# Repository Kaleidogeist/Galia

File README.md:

# Galia
Modular split ergonomic keyboard system with each half consisting of a central motherboard and a hot-swappable key cluster daughterboard to allow for maximum flexibility.

### Motherboard

- Current version: V0.4.
- Schematic [here](https://kicanvas.org/?repo=https%3A%2F%2Fgithub.com%2Fghostlybutterfly%2FGalia%2Fblob%2FV0_dev%2FMotherboard%2FMotherboard.kicad_sch). 
- Board layout [here](https://kicanvas.org/?repo=https%3A%2F%2Fgithub.com%2Fghostlybutterfly%2FGalia%2Ftree%2FV0_dev%2FMotherboard).
### Daughterboard (Cantaloupe)
Current version: N/A (wip).

## Disclaimer
This keyboard is licensed under [CERN-OHL-S-2.0](https://cern-ohl.web.cern.ch/) and is compatible with both [QMK Firmware](https://qmk.fm/) and [ZMK Firmware](https://zmk.dev).

## Key Features
### Motherboard
* Fully reversible, compact (32.0x50.0mm), and designed to fit onto the top inner corner of a split keyboard.
* On-board STM32G0B1CCU7 processor.
* ESD-protected USB-C input port and USB-C split comms port.
* Connects to daughterboard through fully ESD-protected 2.54mm pitch 02x06 pogo header.
* SPI and USART lines terminated with 22ohm to reduce ringing, overshoot and EMI, and improve signal integrity.
* VBUS input rail limited to ~469mA and 5V output rail limited to ~179mA through the use of TPS2553-1 current limiting switches with reverse voltage protection. VBUS requires power cycling to restart the device upon overcurrent, +5V can be power-cycled through firmware with EN pin controlled through firmware to reduce RGB LED quiescent current draw.
* 4-layer (signal/ground/power/signal) PCB and star ground connection point in between USB port shields.
* [Paw-Connect](https://github.com/LeoDJ/Paw-Connect) TC-2030NL SWD header for debugging purposes.
* On-board single-button reset circuit.
* JLC basic assembly compatible as long as USB ports are not soldered on.

### Daughterboard (TBC)
* Matrix scan planned to be implemented through 74HC595 SIPO shift registers for low power draw and compatibility with ZMK interrupt functionality.
* Also compatible with charlieplex, duplex, and standard matrix layouts.
* WS2812 and AP102 (QMK only) LED support.
* Additional [VIK](https://github.com/sadekbaroudi/vik) header support if desired.

## Pogo header pinout
| Function/description                 | Pin name | Row 1 | Row 2 | Pin name | Function/description                  |
| ------------------------------------ | -------- | ----- | ----- | -------- | ------------------------------------- |
| USART2_TX/ADC1_IN2/TIM2_CH3          | A2       | GPIO1 | CS    | B9       | SPI2_NSS/I2C1_SDA/USART3_RX/TIM4_CH4  |
| USART2_RX/ADC1_IN3/TIM2_CH4          | A3       | GPIO2 | SCK   | B8       | SPI2_SCK/I2C1_SCL/USART3_TX/TIM4_CH3  |
| SPI1_SCK/ADC1_IN5/TIM2_CH1           | A5       | GPIO3 | MOSI  | B7       | SPI2_MOSI/I2C1_SDA/USART1_RX/TIM4_CH2 |
| SPI1_MISO/ADC1_IN6/I2C2_SDA/TIM3_CH1 | A6       | GPIO4 | MISO  | B6       | SPI2_MISO/I2C1_SCL/USART1_TX/TIM1_CH3 |
| SPI1_MOSI/ADC1_IN7/I2C2_SCL/TIM3_CH2 | A7       | GPIO5 | +5V   | N/A      | ~207mA max draw by daughterboard      |
| 200mA max draw by this side overall  | N/A      | VDD   | GND   | A7       | GND                                   |

## Changelog
* 2026/10/01: Changed library name and updated paths.
* 2026/09/30: V0.4 motherboard update complete. Removed guard ring around the edge of the board. Moved reset button and pogo header down the board. Increased length back to 50mm to allow for an E73-2G4M08S1C version to be developed if desired. Simplified reset circuit - doesn't use the Acheron version anymore. Reduced number of pins in pogo header, as the largest available ones are 2x06. Pinout of pogo header changed to greatly simplify routing - no longer VIK-compliant. Signalis reference and Paw-Connect added back. Changed file structure.
* 2026/09/26: V0.3 motherboard update complete. Reduced size again, rerouted board and changed shape slightly. Removed one mounting hole and centred the other between the USB ports. Changed input fuse and external +5V output to TPS2553-1 latching power switch with reverse voltage/current protection. Removed AO3401 and LMV321 discrete reverse current protection at VBUS input. Reduced size of VBUS and VSPLIT ferrite bead and transistors in the Acheron reset circuit. Made Acheron reset circuit reach DFU faster. 
* 2026/09/21: V0.2 motherboard update complete. Significantly decreased size. GPIO3, GPIO4 and GPIO5 pins changed. Increased size of pogo pin header pads. Removed extra IO header. Replaced 2x03 2.54mm programming header and TC2030-NL with 2x05 1.27mm Samtec IDC header. Replaced reset switch with smaller Alps SKSNLP mid-mount switch. Added layer marker. Changed repository file structure.
* 2026/09/17: Fixed gap in guard rail.
* 2026/09/16: V0.1 motherboard initial commit.

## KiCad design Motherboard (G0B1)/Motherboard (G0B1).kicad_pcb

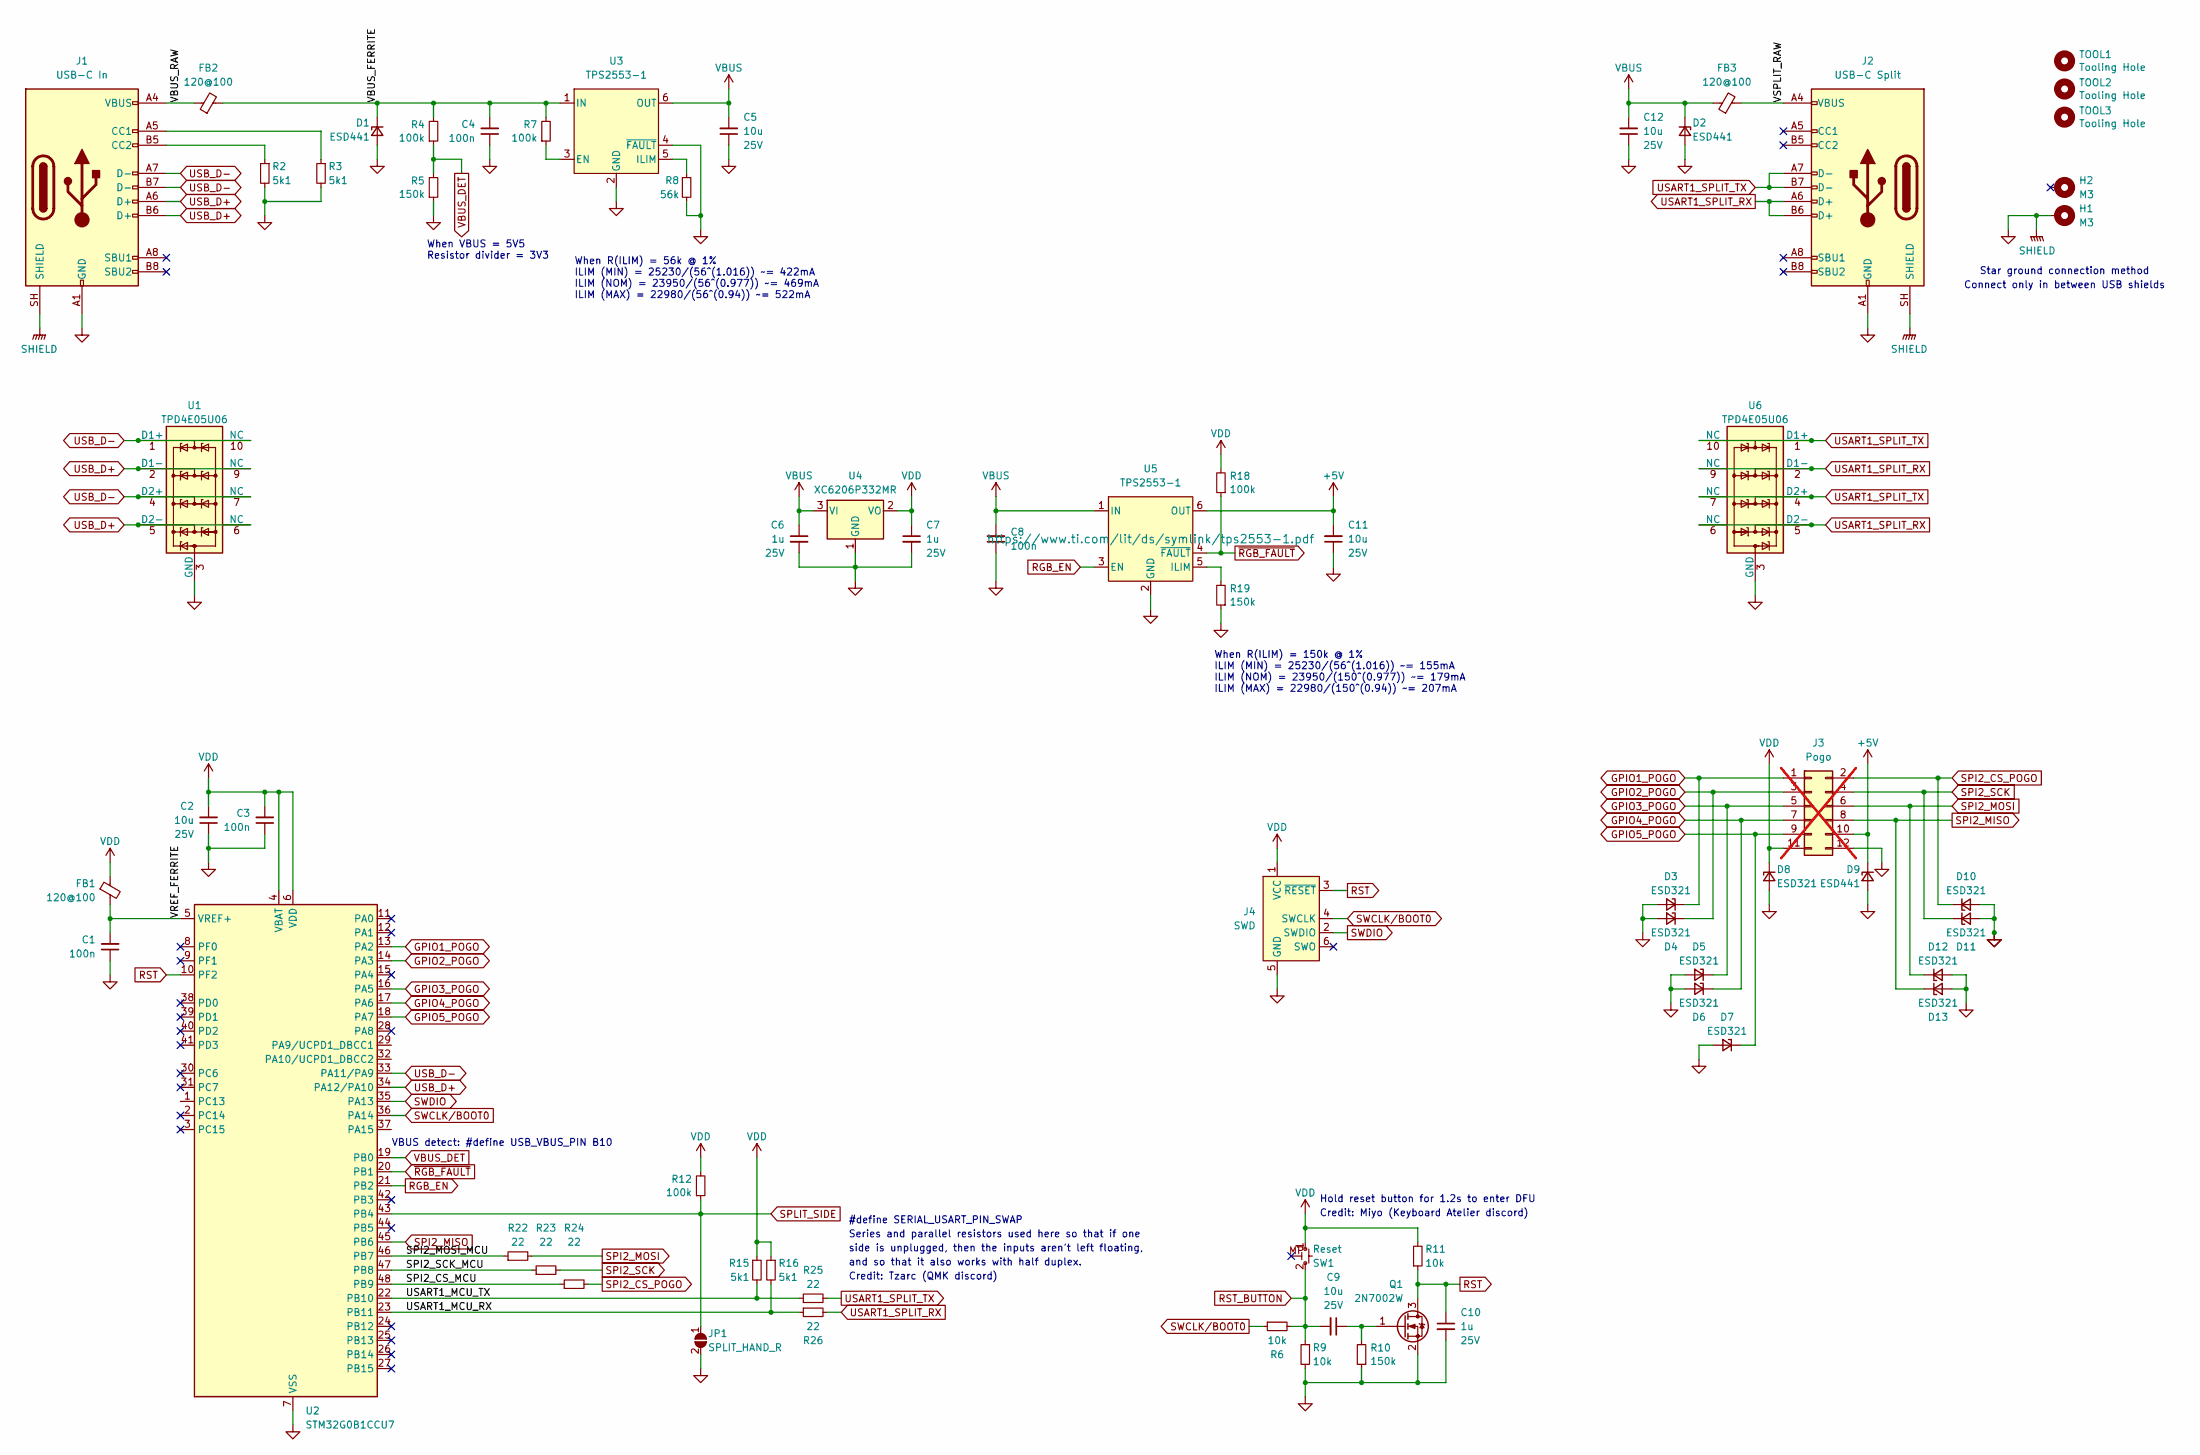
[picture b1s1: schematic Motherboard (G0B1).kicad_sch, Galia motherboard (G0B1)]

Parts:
C1, C3, C4, C8: 100n; C_0402_1005Metric; Rating 50V; MPN CL05B104KB54PNC; LCSC C307331
C2, C5, C9, C11, C12: 10u; C_0603_1608Metric; Rating 25V; MPN CL10A106MA8NRNC; LCSC C96446
C6, C7, C10: 1u; C_0402_1005Metric; Rating 25V; MPN CL05A105KA5NQNC; LCSC C52923
D1, D2, D9: ESD441; X1SON_0.6x1mm_P0.65mm_Texas_DPY0002A; Rating 7V breakdown; MPN ESD441DPYR; LCSC C53161160
D3, D4, D5, D6, D7, D8, D10, D11, D12, D13: ESD321; X1SON_0.6x1mm_P0.65mm_Texas_DPY0002A; Rating 4V5 breakdown; MPN ESD321DPYR; LCSC C2868952
FB1, FB2, FB3: 120@100; L_0402_1005Metric; MPN MPZ1005S121ET000; LCSC C275477
H1, H2: M3; MountingHole_3.2mm_M3_Pad_Via; MPN N/A; LCSC N/A
J1: USB-C In; USB_C_Receptacle_Molex_2169900001; MPN GT-USB-7014D; LCSC C2843969
J2: USB-C Split; USB_C_Receptacle_Molex_2169900001; MPN GT-USB-7014D; LCSC C2843969
J3: Pogo; PinHeader_2x06_2.54mm_MillMax_PogoTarget_419-10-212-00-0010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; not fitted
J4: SWD; Paw-Connect_RevB_TC2030-IDC-NL_2x03_P1.27mm_Vertical
JP1: SPLIT_HAND_R; SolderJumper-2_P1.2mm_Open_Pad1.0x1.4mm; MPN N/A; LCSC N/A
Q1: 2N7002W; SOT-323_SC-70-3; MPN 2N7002W; LCSC C7420322
R2, R3, R15, R16: 5k1; R_0402_1005Metric; MPN 0402WGF5101TCE; LCSC C25905
R4, R7, R12, R18: 100k; R_0402_1005Metric; MPN 0402WGF1003TCE; LCSC C25741
R5, R10, R19: 150k; R_0402_1005Metric; MPN 0402WGF1503TCE; LCSC C25755
R6, R9, R11: 10k; R_0402_1005Metric; MPN 0402WGF1002TCE; LCSC C25744
R8: 56k; R_0402_1005Metric; MPN 0402WGF5602TCE; LCSC C25796
R22, R23, R24, R25, R26: 22; R_0402_1005Metric; MPN 0402WGF220JTCE; LCSC C25092
SW1: Reset; SW_Alps_SKSNLM_SKSNLP; MPN SKSNLPE010; LCSC C53113391
TOOL1, TOOL2, TOOL3: Tooling Hole; MountingHole_JLC-Tooling; MPN N/A; LCSC N/A
U1, U6: TPD4E05U06; USON-10_2.5x1.0mm_P0.5mm; MPN TPD4E05U06QDQARQ1; LCSC C81353
U2: STM32G0B1CCU7; QFN-48-1EP_7x7mm_P0.5mm_EP5.6x5.6mm; MPN STM32G0B1CCU7; LCSC C29759424
U3, U5: TPS2553-1; WSON-6-1EP_2x2mm_P0.65mm_EP1x1.6mm; MPN TPS2553DRVR-1; LCSC C411878
U4: XC6206P332MR; SOT-23-3; MPN XC6206P332MR-G; LCSC C5446

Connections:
+5V: C11.2, D9.1 (K), J3.10, U5.6 (OUT)
/SPI2_CS_MCU: R24.1, U2.48 (PB9)
/SPI2_MOSI_MCU: R22.1, U2.46 (PB7)
/SPI2_SCK_MCU: R23.1, U2.47 (PB8)
/USART1_MCU_RX: R16.2, R26.1, U2.23 (PB11)
/USART1_MCU_TX: R15.2, R25.1, U2.22 (PB10)
/VBUS_FERRITE: C4.2, D1.1 (K), FB2.2, R4.2, R7.2, U3.1 (IN)
/VBUS_RAW: FB2.1, J1.A4 (VBUS), J1.A9 (VBUS), J1.B4 (VBUS), J1.B9 (VBUS)
/VREF_FERRITE: C1.2, FB1.2, U2.5 (VREF+)
/VSPLIT_RAW: FB3.2, J2.A4 (VBUS), J2.A9 (VBUS), J2.B4 (VBUS), J2.B9 (VBUS)
GND: C1.1, C2.1, C3.1, C4.1, C5.1, C6.2, C7.2, C8.1, C10.2, C11.1, C12.1, D1.2 (A), D2.2 (A), D3.2 (A), D4.2 (A), D5.2 (A), D6.2 (A), D7.2 (A), D8.2 (A), D9.2 (A), D10.2 (A), D11.2 (A), D12.2 (A), D13.2 (A), H1.1 (1_1), J1.A1 (GND), J1.A12 (GND), J1.B1 (GND), J1.B12 (GND), J1.SH (SHIELD), J2.A1 (GND), J2.A12 (GND), J2.B1 (GND), J2.B12 (GND), J2.SH (SHIELD), J3.12, J4.5 (GND), JP1.2 (B), Q1.2 (S), R2.2, R3.2, R5.1, R8.2, R9.2, R10.1, R19.1, U1.3 (GND), U1.8 (GND), U2.7 (VSS), U2.49 (VSS), U3.2 (GND), U3.4 (~FAULT), U3.7 (EP), U4.1 (GND), U5.2 (GND), U5.7 (EP), U6.3 (GND), U6.8 (GND)
GPIO1_POGO: D3.1 (K), J3.1, U2.13 (PA2)
GPIO2_POGO: D4.1 (K), J3.3, U2.14 (PA3)
GPIO3_POGO: D5.1 (K), J3.5, U2.16 (PA5)
GPIO4_POGO: D6.1 (K), J3.7, U2.17 (PA6)
GPIO5_POGO: D7.1 (K), J3.9, U2.18 (PA7)
unnamed: J1.A5 (CC1), R3.1
unnamed: J1.B5 (CC2), R2.1
unnamed: C9.1, Q1.1 (G), R10.2
unnamed: R7.1, U3.3 (EN)
unnamed: R8.1, U3.5 (ILIM)
unnamed: R19.2, U5.5 (ILIM)
RGB_EN: U2.21 (PB2), U5.3 (EN)
RST: C10.1, J4.3 (~RESET), Q1.3 (D), R11.1, U2.10 (PF2)
RST_BUTTON: C9.2, R6.2, R9.1, SW1.2 (B)
SPI2_CS_POGO: D10.1 (K), J3.2, R24.2
SPI2_MISO: D13.1 (K), J3.8, U2.45 (PB6)
SPI2_MOSI: D12.1 (K), J3.6, R22.2
SPI2_SCK: D11.1 (K), J3.4, R23.2
SPLIT_SIDE: JP1.1 (A), R12.1, U2.43 (PB4)
SWCLK/BOOT0: J4.4 (SWCLK), R6.1, U2.36 (PA14)
SWDIO: J4.2 (SWDIO), U2.35 (PA13)
USART1_SPLIT_RX: J2.A6 (D+), J2.B6 (D+), R26.2, U6.2 (D1-), U6.5 (D2-), U6.6 (NC), U6.9 (NC)
USART1_SPLIT_TX: J2.A7 (D-), J2.B7 (D-), R25.2, U6.1 (D1+), U6.4 (D2+), U6.7 (NC), U6.10 (NC)
USB_D+: J1.A6 (D+), J1.B6 (D+), U1.2 (D1-), U1.5 (D2-), U1.6 (NC), U1.9 (NC), U2.34 (PA12/PA10)
USB_D-: J1.A7 (D-), J1.B7 (D-), U1.1 (D1+), U1.4 (D2+), U1.7 (NC), U1.10 (NC), U2.33 (PA11/PA9)
VBUS: C5.2, C6.1, C8.2, C12.2, D2.1 (K), FB3.1, U3.6 (OUT), U4.3 (VI), U5.1 (IN)
VBUS_DET: R4.1, R5.2, U2.19 (PB0)
VDD: C2.2, C3.2, C7.1, D8.1 (K), FB1.1, J3.11, J4.1 (VCC), R11.2, R12.2, R15.1, R16.1, R18.2, SW1.1 (A), U2.4 (VBAT), U2.6 (VDD), U4.2 (VO)
~RGB_FAULT: R18.1, U2.20 (PB1), U5.4 (~FAULT)

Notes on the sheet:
When R(ILIM) = 56k @ 1% ILIM (MIN) = 25230/(56^(1.016)) ~= 422mA ILIM (NOM) = 23950/(56^(0.977)) ~= 469mA ILIM (MAX) = 22980/(56^(0.94)) ~= 522mA
Credit: Tzarc (QMK discord)
Hold reset button for 1.2s to enter DFU
Series and parallel resistors used here so that if one
VBUS detect: #define USB_VBUS_PIN B10
Credit: Miyo (Keyboard Atelier discord)
side is unplugged, then the inputs aren't left floating,
and so that it also works with half duplex.
When VBUS = 5V5 Resistor divider = 3V3
Connect only in between USB shields
#define SERIAL_USART_PIN_SWAP
When R(ILIM) = 150k @ 1% ILIM (MIN) = 25230/(56^(1.016)) ~= 155mA ILIM (NOM) = 23950/(150^(0.977)) ~= 179mA ILIM (MAX) = 22980/(150^(0.94)) ~= 207mA
Star ground connection method

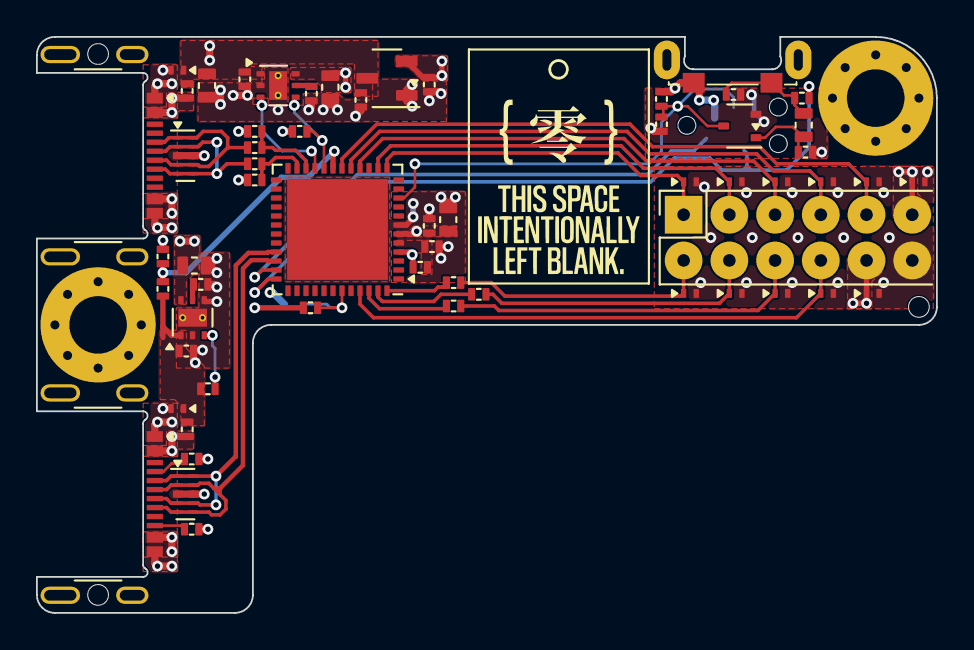
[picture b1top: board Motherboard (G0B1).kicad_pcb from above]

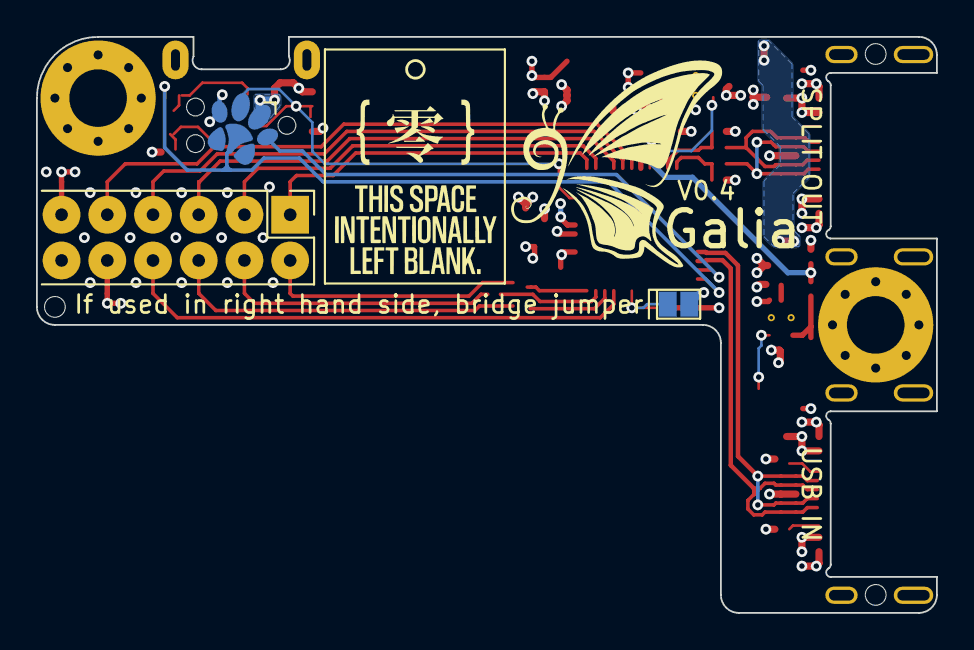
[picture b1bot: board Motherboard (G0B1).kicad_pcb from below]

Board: 4 copper layers, 50.0 x 32.0 mm, 66 parts (2 on the bottom side), 40 nets.

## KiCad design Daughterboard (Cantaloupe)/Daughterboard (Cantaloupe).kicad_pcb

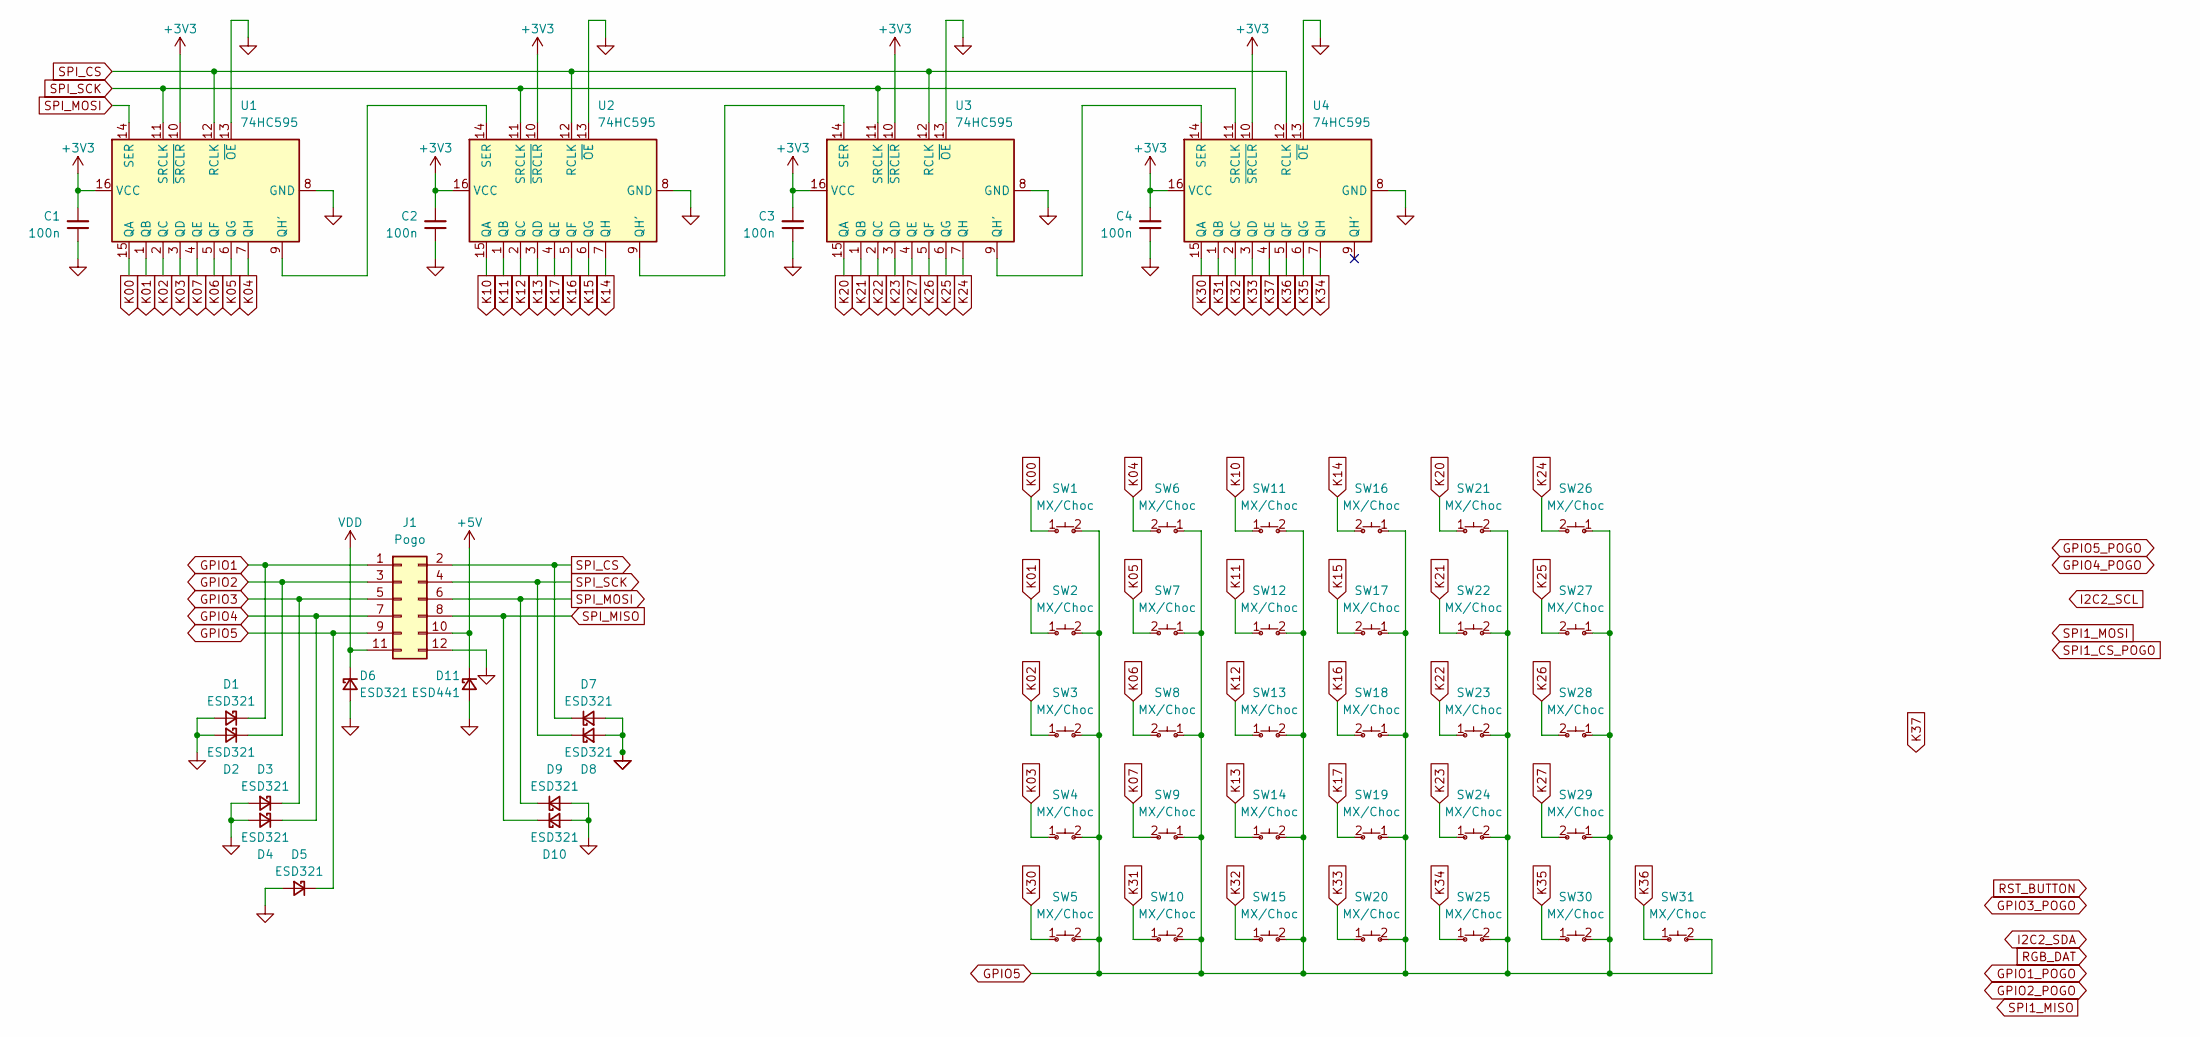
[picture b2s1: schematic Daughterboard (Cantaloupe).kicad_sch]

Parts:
C1, C2, C3, C4: 100n; C_0402_1005Metric; Voltage 50V; MPN CL05B104KB54PNC; LCSC C307331
D1, D2, D3, D4, D5, D6, D7, D8, D9, D10: ESD321; X1SON_0.6x1mm_P0.65mm_Texas_DPY0002A; Rating 4V5 breakdown; MPN ESD321DPYR; LCSC C2868952
D11: ESD441; X1SON_0.6x1mm_P0.65mm_Texas_DPY0002A; Rating 7V breakdown; MPN ESD441DPYR; LCSC C53161160
J1: Pogo; PinHeader_2x06_2.54mm_MillMax_PogoPin_823-22-012-10-000101-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
SW1, SW2, SW3, SW4, SW5, SW6, SW7, SW8, SW9, SW10, SW11, SW12, SW13, SW14, SW15, SW16, SW17, SW18, SW19, SW20, SW21, SW22, SW23, SW24, SW25, SW26, SW27, SW28, SW29, SW30, SW31: MX/Choc; SW_KB_Choc-KS33_1U_Hotswap_Reversible
U1, U2, U3, U4: 74HC595; DHVQFN-16-1EP_2.5x3.5mm_P0.5mm_EP1x2mm; MPN 74HC595BQ,115; LCSC C730243

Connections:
+3V3: C1.2, C2.2, C3.2, C4.2, U1.10 (~SRCLR), U1.16 (VCC), U2.10 (~SRCLR), U2.16 (VCC), U3.10 (~SRCLR), U3.16 (VCC), U4.10 (~SRCLR), U4.16 (VCC)
+5V: D11.1 (K), J1.10
GND: C1.1, C2.1, C3.1, C4.1, D1.2 (A), D2.2 (A), D3.2 (A), D4.2 (A), D5.2 (A), D6.2 (A), D7.2 (A), D8.2 (A), D9.2 (A), D10.2 (A), D11.2 (A), J1.12, U1.8 (GND), U1.13 (~OE), U1.17 (EP), U2.8 (GND), U2.13 (~OE), U2.17 (EP), U3.8 (GND), U3.13 (~OE), U3.17 (EP), U4.8 (GND), U4.13 (~OE), U4.17 (EP)
GPIO1: D1.1 (K), J1.1
GPIO2: D2.1 (K), J1.3
GPIO3: D3.1 (K), J1.5
GPIO4: D4.1 (K), J1.7
GPIO5: D5.1 (K), J1.9, SW1.2 (B), SW2.2 (B), SW3.2 (B), SW4.2 (B), SW5.2 (B), SW6.1 (A), SW7.1 (A), SW8.1 (A), SW9.1 (A), SW10.2 (B), SW11.2 (B), SW12.2 (B), SW13.2 (B), SW14.2 (B), SW15.2 (B), SW16.1 (A), SW17.1 (A), SW18.1 (A), SW19.1 (A), SW20.2 (B), SW21.2 (B), SW22.2 (B), SW23.2 (B), SW24.2 (B), SW25.2 (B), SW26.1 (A), SW27.1 (A), SW28.1 (A), SW29.1 (A), SW30.2 (B), SW31.2 (B); also elsewhere on the board
K00: SW1.1 (A), U1.15 (QA); also elsewhere on the board
K01: SW2.1 (A), U1.1 (QB)
K02: SW3.1 (A), U1.2 (QC)
K03: SW4.1 (A), U1.3 (QD)
K04: SW6.2 (B), U1.7 (QH)
K05: SW7.2 (B), U1.6 (QG)
K06: SW8.2 (B), U1.5 (QF)
K07: SW9.2 (B), U1.4 (QE)
K10: SW11.1 (A), U2.15 (QA)
K11: SW12.1 (A), U2.1 (QB)
K12: SW13.1 (A), U2.2 (QC)
K13: SW14.1 (A), U2.3 (QD)
K14: SW16.2 (B), U2.7 (QH)
K15: SW17.2 (B), U2.6 (QG)
K16: SW18.2 (B), U2.5 (QF)
K17: SW19.2 (B), U2.4 (QE)
K20: SW21.1 (A), U3.15 (QA)
K21: SW22.1 (A), U3.1 (QB)
K22: SW23.1 (A), U3.2 (QC)
K23: SW24.1 (A), U3.3 (QD)
K24: SW26.2 (B), U3.7 (QH)
K25: SW27.2 (B), U3.6 (QG)
K26: SW28.2 (B), U3.5 (QF)
K27: SW29.2 (B), U3.4 (QE)
K30: SW5.1 (A), U4.15 (QA)
K31: SW10.1 (A), U4.1 (QB)
K32: SW15.1 (A), U4.2 (QC)
K33: SW20.1 (A), U4.3 (QD)
K34: SW25.1 (A), U4.7 (QH)
K35: SW30.1 (A), U4.6 (QG)
K36: SW31.1 (A), U4.5 (QF)
K37: U4.4 (QE)
unnamed: U1.9 (QH'), U2.14 (SER)
unnamed: U2.9 (QH'), U3.14 (SER)
unnamed: U3.9 (QH'), U4.14 (SER)
SPI_CS: D7.1 (K), J1.2, U1.12 (RCLK), U2.12 (RCLK), U3.12 (RCLK), U4.12 (RCLK)
SPI_MISO: D10.1 (K), J1.8
SPI_MOSI: D9.1 (K), J1.6, U1.14 (SER)
SPI_SCK: D8.1 (K), J1.4, U1.11 (SRCLK), U2.11 (SRCLK), U3.11 (SRCLK), U4.11 (SRCLK)
VDD: D6.1 (K), J1.11

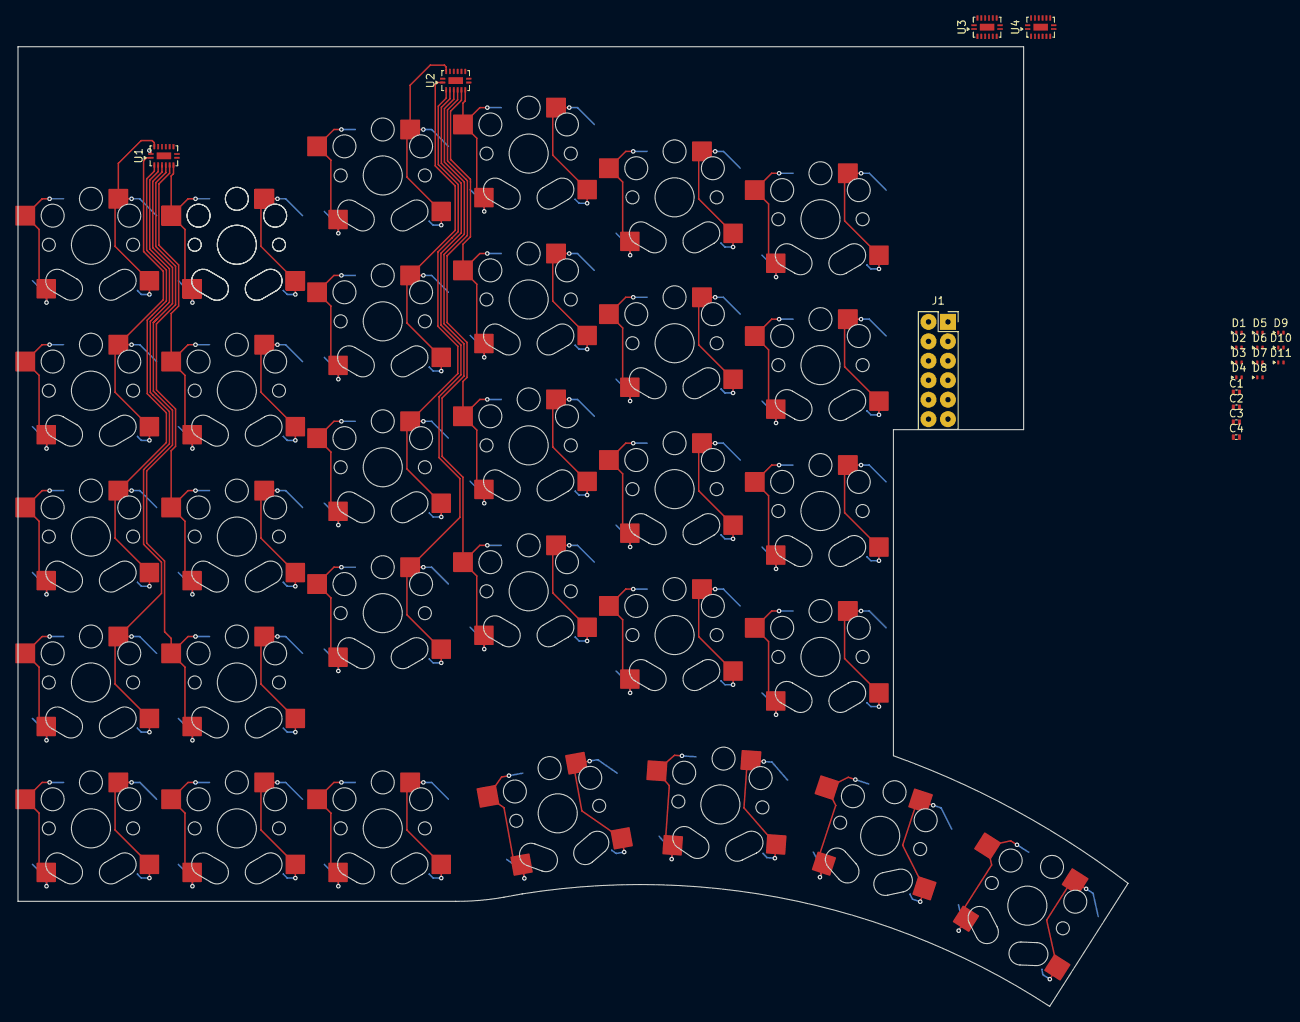
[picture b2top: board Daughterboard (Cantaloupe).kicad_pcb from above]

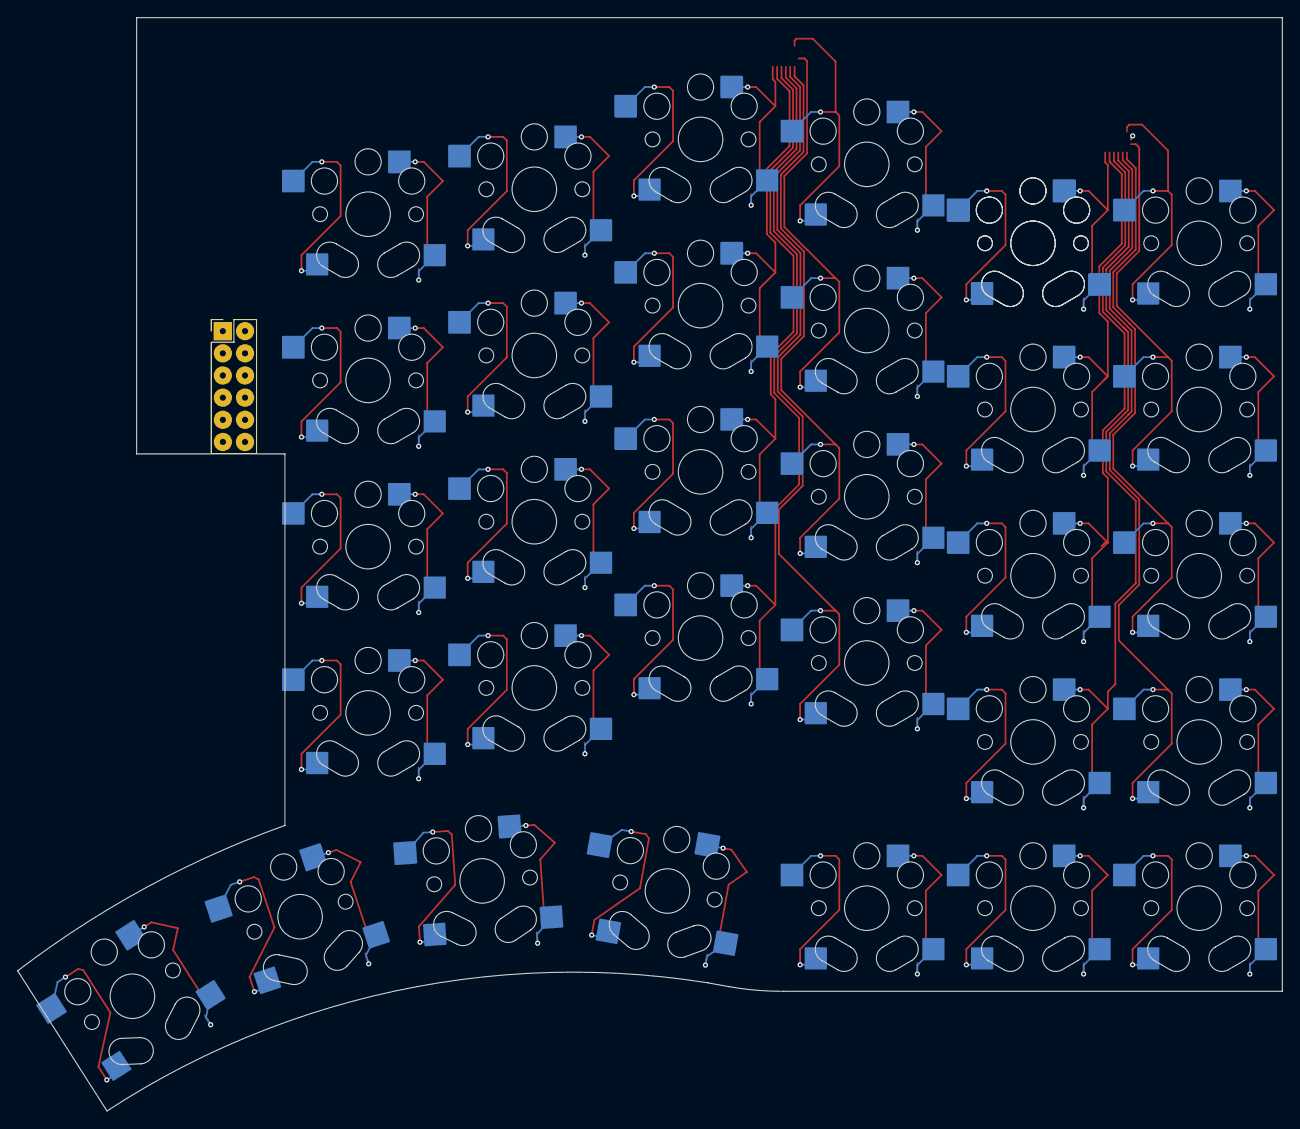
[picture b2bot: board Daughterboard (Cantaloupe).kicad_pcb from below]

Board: 2 copper layers, 144.9 x 125.3 mm, 52 parts (32 on the bottom side), 47 nets.

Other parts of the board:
SW1#2: MX/Choc; SW_KB_Choc-KS33_1U_Hotswap_Reversible

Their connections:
GPIO5: SW1#2.2 (B); also elsewhere on the board
K00: SW1#2.1 (A); also elsewhere on the board
